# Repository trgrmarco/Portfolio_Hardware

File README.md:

# Portfolio_Hardware
Hi, this is my portfolio with some of the designs i have done

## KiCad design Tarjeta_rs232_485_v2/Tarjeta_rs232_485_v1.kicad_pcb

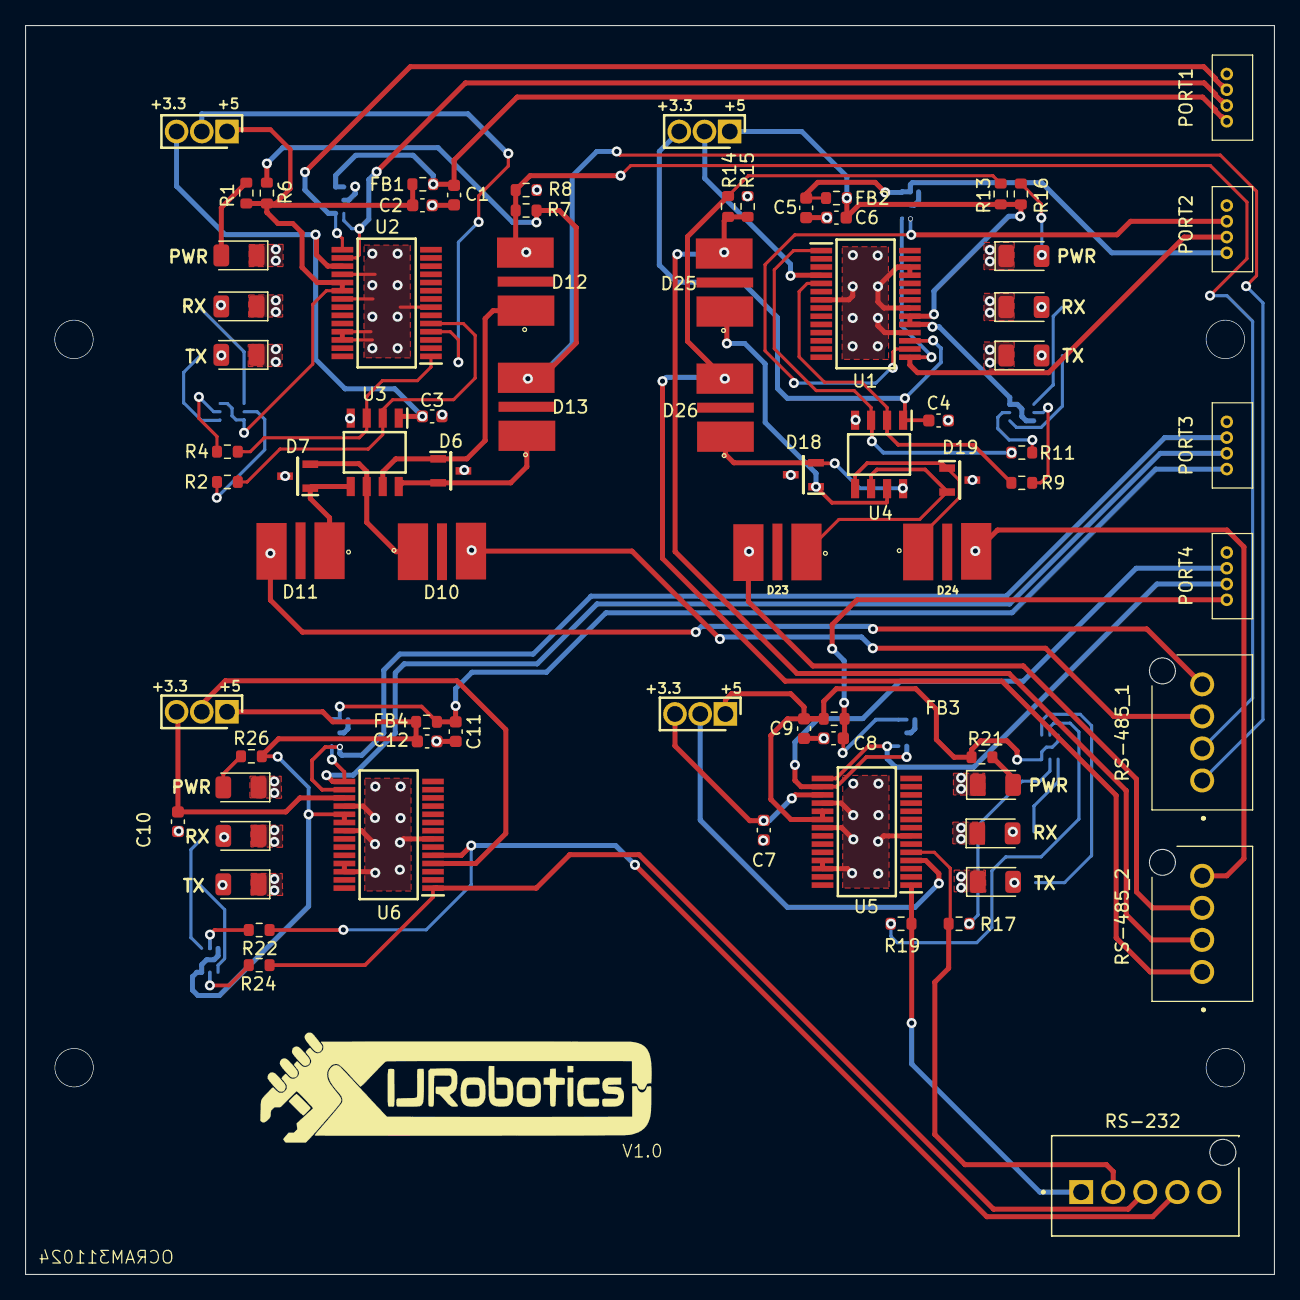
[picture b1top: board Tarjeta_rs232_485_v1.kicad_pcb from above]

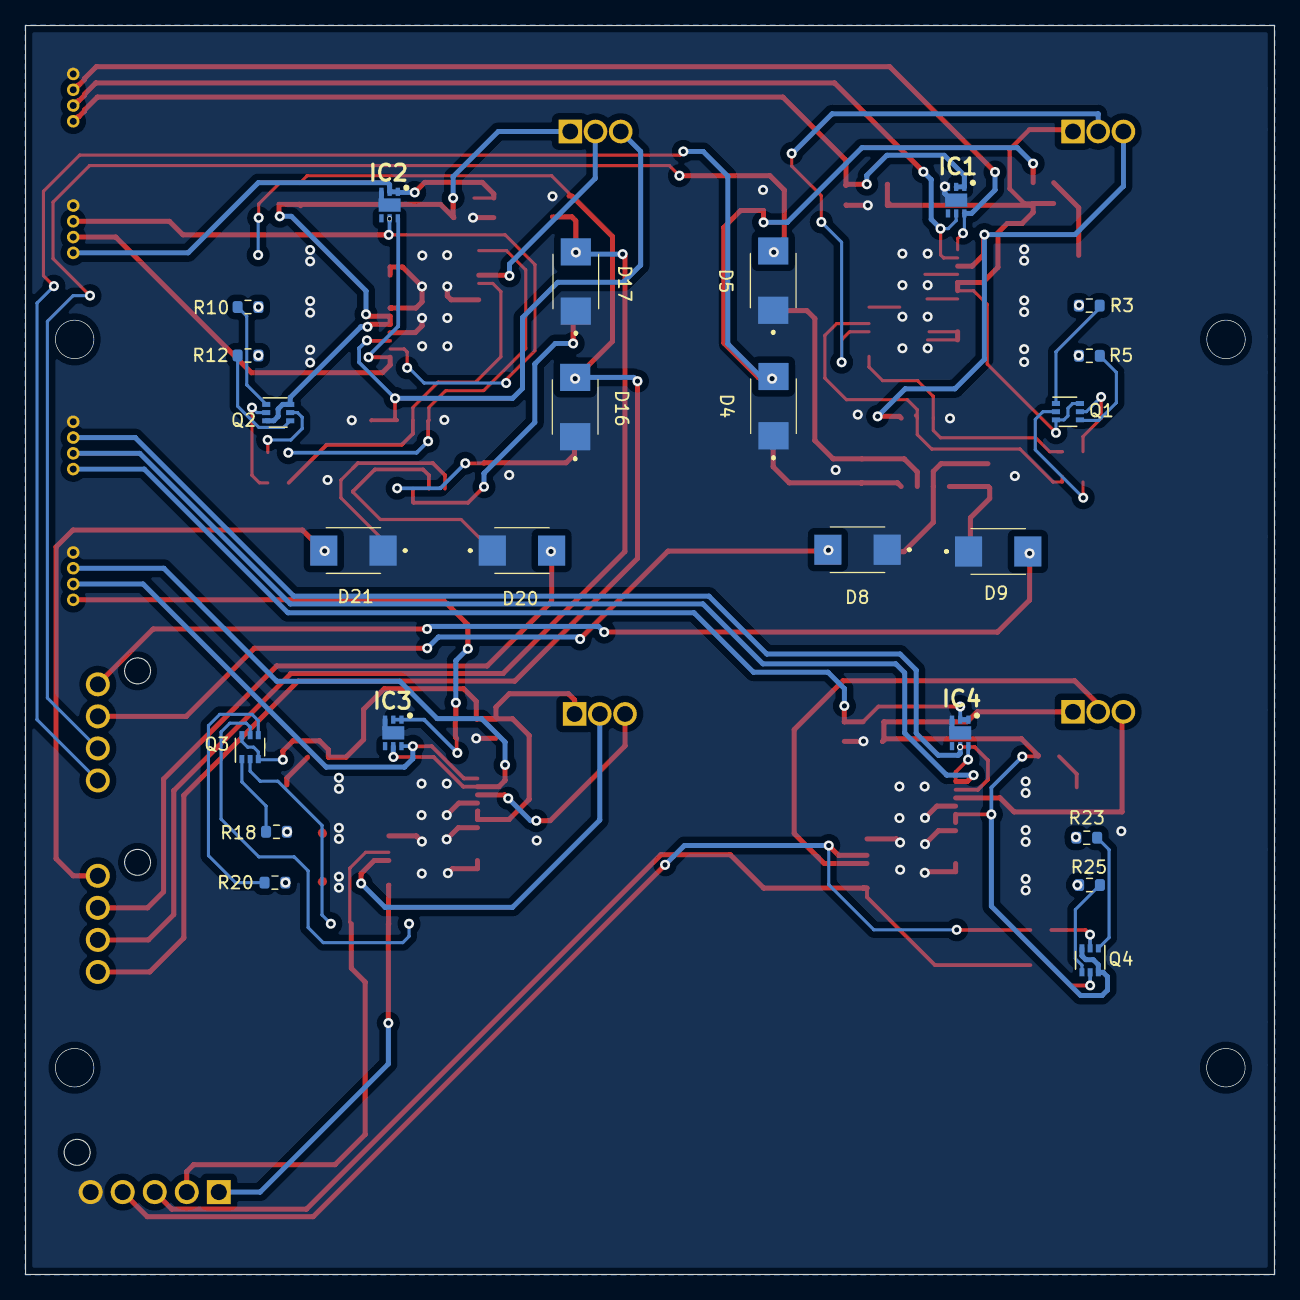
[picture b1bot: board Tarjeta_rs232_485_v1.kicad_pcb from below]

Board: 2 copper layers, 99.0 x 99.0 mm, 99 parts (24 on the bottom side), 77 nets.

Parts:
+3.3     +5, +3.3    +5, +3.3    +5#2, +3.3    +5#3: Conn_01x03; JUMPER 3POS
C1, C5, C8, C11: 10nF; C_0603_1608Metric
C2, C6, C9, C12: 4.7uF; C_0603_1608Metric
C3, C4, C7, C10: 0.1uF; C_0603_1608Metric
D4, D5, D8, D9, D16, D17, D20, D21: TISP4240M3BJR-S; TISP4240M3BJRS
D6, D7, D18, D19: CDSOT23-SM712
D10, D11, D12, D13, D23, D24, D25, D26: TBU-CA065-200-WH-; TBU-CA065-200-WH
FB1, FB2, FB3, FB4: 60 ohms; R_0603_1608Metric
IC1, IC2, IC3, IC4: D5V0F3B6LP20-7
PORT1, PORT2, PORT3, PORT4: Conn_01x04; 530470410
PWR: LED; LED_1206_3216Metric
PWR#2, PWR#3, PWR#4: LED; LED_1206_3216Metric
Q1, Q2, Q3, Q4: MBT3906DW1; SOT-363_SC-70-6
R1, R3, R5, R10, R12, R16, R18, R20, R21, R23, R25, R26: 330; R_0603_1608Metric
R2, R4, R9, R11, R17, R19, R22, R24: 10K; R_0603_1608Metric
R6, R8, R13, R15: 560; R_0603_1608Metric
R7, R14: 120; R_0603_1608Metric
RS-232: Conn_01x05; 2-644486-5
RS-485_1, RS-485_2: Conn_01x04; 26444864
RX: LED; LED_1206_3216Metric
RX#2, RX#3, RX#4: LED; LED_1206_3216Metric
TX: LED; LED_1206_3216Metric
TX#2, TX#3, TX#4: LED; LED_1206_3216Metric
U1, U2, U5, U6: FT232RNL-TUBE
U3, U4: ADM3490ExR; ADM3490

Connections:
+3.3V_1: +3.3 +5#3.3, C3.1, U2.17, U3.1
+3.3V_2: +3.3 +5#2.3, C4.1, U1.17, U4.1
+3.3V_3: +3.3 +5.3, C7.1, U5.17
+3.3V_4: +3.3 +5.3, C10.1, U6.17
+5V_1: +3.3 +5#3.1, C2.1, FB1.1, Q1.3, Q1.6, R1.2, R6.2, U2.19, U2.20
+5V_2: +3.3 +5#2.1, C6.1, FB2.1, Q2.3, Q2.6, R13.2, R16.2, U1.19, U1.20
+5V_3: +3.3 +5.1, C9.1, FB3.1, Q3.3, Q3.6, R21.2, U5.19, U5.20
+5V_4: +3.3 +5.1, C12.1, FB4.1, Q4.3, Q4.6, R26.2, U6.19, U6.20
+5V_USB_1: C1.1, FB1.2, IC1.1, IC1.2, PORT1.1
+5V_USB_2: C5.1, FB2.2, IC2.1, IC2.2, PORT2.1
+5V_USB_3: C8.1, FB3.2, IC3.1, IC3.2, PORT4.1
+5V_USB_4: C11.1, FB4.2, IC4.1, IC4.2, PORT3.1
AP_1: D6.2, D13.1, U3.8
AP_2: D18.2, D26.1, U4.8
A_1: D4.2, D13.3, R6.1, R7.2, RS-485_1.1
A_2: D16.2, D26.3, R13.1, R14.2, RS-485_2.1
BP_1: D6.1, D12.1, U3.7
BP_2: D18.1, D25.1, U4.7
B_1: D5.2, D12.3, R7.1, R8.2, RS-485_1.2
B_2: D17.2, D25.3, R14.1, R15.2, RS-485_2.2
D+_1: IC1.6, PORT1.3, U2.15
D+_2: IC2.6, PORT2.2, U1.15
D+_3: IC3.6, PORT4.2, U5.15
D+_4: IC4.6, PORT3.2, U6.15
D-_1: IC1.5, PORT1.2, U2.16
D-_2: IC2.5, PORT2.3, U1.16
D-_3: IC3.5, PORT4.3, U5.16
D-_4: IC4.5, PORT3.3, U6.16
GND: C1.2, C2.2, C3.2, C4.2, C5.2, C6.2, C7.2, C8.2, C9.2, C10.2, C11.2, C12.2, D4.1, D5.1, D6.3, D7.3, D8.1, D9.1, D16.1, D17.1, D18.3, D19.3, D20.1, D21.1, IC1.3, IC1.7, IC2.3, IC2.7, IC3.3, IC3.7, IC4.3, IC4.7, PORT1.4, PORT2.4, PORT3.4, PORT4.4, PWR.1, PWR#2.1, PWR#3.1, PWR#4.1, R8.1, R15.1, RS-232.5, RX.1, RX#2.1, RX#3.1, RX#4.1, TX.1, TX#2.1, TX#3.1, TX#4.1, U1.7, U1.18, U1.21, U1.25, U1.26, U2.7, U2.18, U2.21, U2.25, U2.26, U3.4, U4.4, U5.7, U5.18, U5.21, U5.25, U5.26, U6.7, U6.18, U6.21, U6.25, U6.26
unnamed: PWR#4.2, R1.1
unnamed: R3.2, RX#4.2
unnamed: R5.2, TX#4.2
unnamed: R10.2, RX#3.2
unnamed: R12.2, TX#3.2
unnamed: PWR#3.2, R16.1
unnamed: R18.2, RX#2.2
unnamed: R20.2, TX#2.2
unnamed: PWR#2.2, R21.1
unnamed: R23.2, RX.2
unnamed: R25.2, TX.2
unnamed: PWR.2, R26.1
unnamed: Q1.1, R3.1
unnamed: Q1.2, R2.1
unnamed: Q1.4, R5.1
unnamed: Q1.5, R4.1
unnamed: Q2.1, R10.1
unnamed: Q2.2, R9.1
unnamed: Q2.4, R12.1
unnamed: Q2.5, R11.1
unnamed: Q3.1, R18.1
unnamed: Q3.2, R17.1
unnamed: Q3.4, R20.1
unnamed: Q3.5, R19.1
unnamed: Q4.1, R23.1
unnamed: Q4.2, R22.1
unnamed: Q4.4, R25.1
unnamed: Q4.5, R24.1
RX_485_1: R2.2, U2.5, U3.2
RX_REEL: R22.2, RS-232.4, U6.5
RX_REEL_1: R17.2, RS-232.2, U5.5
RX_ROBOT: R9.2, U1.5, U4.2
TX_485_1: R4.2, U2.1, U3.3
TX_REEL: R24.2, RS-232.3, U6.1
TX_REEL_1: R19.2, RS-232.1, U5.1
TX_ROBOT: R11.2, U1.1, U4.3
VCCIO_1: +3.3 +5#3.2, U2.4
VCCIO_2: +3.3 +5#2.2, U1.4
VCCIO_3: +3.3 +5.2, U5.4
VCCIO_4: +3.3 +5.2, U6.4
YP_1: D7.1, D11.1, U3.5
YP_2: D19.1, D24.1, U4.5
Y_1: D9.2, D11.3, RS-485_1.4
Y_2: D21.2, D24.3, RS-485_2.4
ZP_1: D7.2, D10.1, U3.6
ZP_2: D19.2, D23.1, U4.6
Z_1: D8.2, D10.3, RS-485_1.3
Z_2: D20.2, D23.3, RS-485_2.3

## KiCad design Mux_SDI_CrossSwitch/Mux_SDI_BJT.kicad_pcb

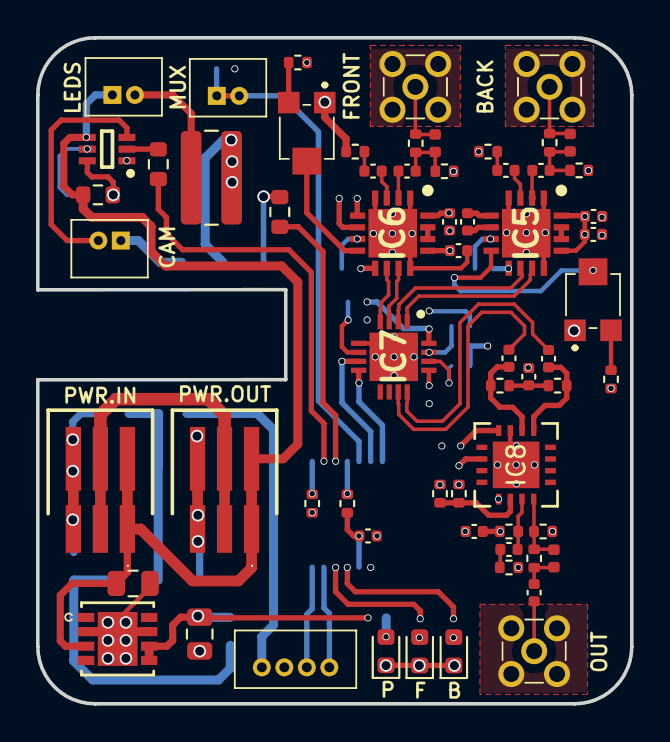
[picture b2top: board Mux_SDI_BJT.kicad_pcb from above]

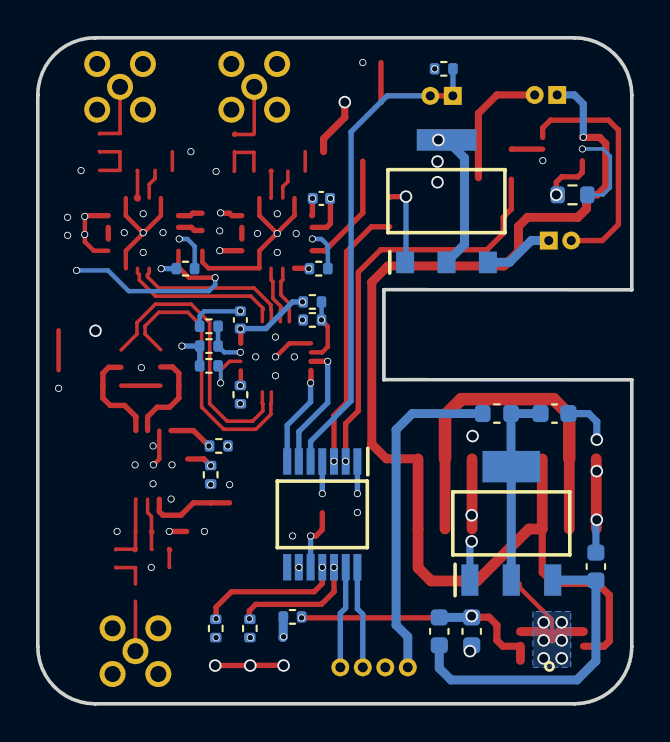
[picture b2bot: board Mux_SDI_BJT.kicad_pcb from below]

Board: 4 copper layers, 33.0 x 37.0 mm, 88 parts (25 on the bottom side), 71 nets.

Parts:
C1: 0.47uF; C_0805_2012Metric
C2: 22uF; C_0805_2012Metric
C3, C4, C5, C6, C7, C8, C9, C10, C11, C12, C13, C14, C15, C16: 1uF; C_0402_1005Metric
C17: 0.1uF; C_0402_1005Metric
C18, C19: 4.7uF; C_0402_1005Metric
C20: 1uF; C_0603_1608Metric
C21, C22: 10uF; C_0603_1608Metric
C23: 100nF; C_0402_1005Metric
D1, D2, D3: LED; LED_0603_1608Metric
F1: .8A; Fuse_0603_1608Metric
FB1: 1K; C_0603_1608Metric
IC1: FFB2227A; SOT65P210X110-6N
IC5, IC6: LMH0344SQ_NOPB
IC7: DS25CP102TSQ_NOPB; DS25CP102TSQNOPB
IC8: LMH0302SQ; LMH0302SQNOPB
IC9: STM32L011D3P6
J1: FRONT; 734151472
J2, J3, J10: 53047-0210
J4: BACK; 734151472
J5: OUT; 734151472
J6, J7: 87438-0343; 874380343
J12: Conn_01x04; 530470410
L1, L2: 5.6nH; L_0402_1005Metric
L3: 6.8nH; L_0402_1005Metric
PS1: LM2940LD-5.0_NOPB; DFN400X400X80-9N
Q1: NJT4031NT1G
R1: 1.7K; R_0603_1608Metric
R2, R3, R4: 1K; R_0603_1608Metric
R5: 33, 1W; R_1020_2550Metric
R6: 560; R_0402_1005Metric
R7, R8, R11, R18, R19, R23: 10K; R_0402_1005Metric
R9, R10: 330; R_0402_1005Metric
R12, R13, R14, R15, R36, R37, R38, R39: 75; R_0402_1005Metric
R16, R17: 37.4; R_0402_1005Metric
R20, R21: 5.6K; R_0402_1005Metric
R22: 750; R_0402_1005Metric
R24, R25, R26, R27, R28, R29, R31, R32: 0; R_0402_1005Metric
R34, R35: 50; R_0402_1005Metric
RV1, RV2: 10K; 35WR100KLFTR
U1: AMS1117-3.3; REG1117-3.3

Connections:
+3.3V: C8.1, C10.1, C11.2, C12.2, C13.2, C14.1, C23.2, F1.2, IC5.13, IC5.16, IC6.13, IC6.16, IC7.16, IC8.9, IC9.10, J12.4, R7.1, R20.1, R21.1, R22.2, R23.2, R24.1, R26.1, R28.1, R32.1, R36.2, R38.1
+5V: C2.1, C20.1, FB1.1, PS1.5, PS1.6, R6.2
+12V: C1.1, IC1.4, J2.1, J6.1, J6.4, J7.1, J7.4, PS1.3, R4.2
+24V: J6.2, J6.5, J7.2, J7.5
+CAM: IC1.3, J3.2
+VIDEO_IN0: J1.1, L2.1, R13.2
+VIDEO_IN1: J4.1, L1.1, R12.2
B_CAMON: IC9.2, R2.2
EN0: IC7.14, R32.2
EN1: IC7.13, R31.2
EQ: IC7.6, R26.2, R27.2
GND: C1.2, C2.2, C8.2, C10.2, C11.1, C12.1, C13.1, C14.2, C17.1, C20.2, C21.2, C22.2, C23.1, D1.1, D2.1, D3.1, IC1.1, IC5.1, IC5.4, IC5.9, IC5.12, IC5.17, IC6.1, IC6.4, IC6.9, IC6.12, IC6.17, IC7.5, IC7.17, IC8.3, IC8.17, IC9.9, J1.2, J1.3, J1.4, J1.5, J3.1, J4.2, J4.3, J4.4, J4.5, J5.2, J5.3, J5.4, J5.5, J6.3, J6.6, J7.3, J7.6, J12.3, PS1.2, PS1.7, PS1.9, Q1.3, R8.2, R11.1, R14.1, R15.1, R16.1, R17.1, R18.2, R19.2, R25.1, R27.1, R29.1, R31.1, R37.1, RV1.1, RV2.1, U1.1
IN_MUX: IC9.5, J10.1, J10.2, R11.2
LED: J2.2, R5.1
LEDS_HIGH: IC9.3, R1.2
LED_BACK: IC9.12, R10.1
LED_FRONT: IC9.11, R9.2
NRST: IC9.4, R7.2
unnamed: C3.1, IC5.2
unnamed: C3.2, L1.2, R12.1, R14.2
unnamed: C4.1, IC6.2
unnamed: C4.2, L2.2, R13.1, R15.2
unnamed: C5.1, IC5.3
unnamed: C5.2, R16.2
unnamed: C6.1, IC6.3
unnamed: C6.2, R17.2
unnamed: C7.1, IC5.6
unnamed: C7.2, IC5.5
unnamed: C9.1, IC6.6
unnamed: C9.2, IC6.5
unnamed: C17.2, R34.1, R35.2
unnamed: C18.1, R37.2
unnamed: C18.2, IC8.11, R36.1
unnamed: C19.2, L3.2, R39.2
unnamed: C21.1, FB1.2, U1.3
unnamed: C22.1, F1.1, U1.2, U1.4
unnamed: D1.2, R6.1
unnamed: D2.2, R9.1
unnamed: D3.2, R10.2
unnamed: IC1.2, R2.1
unnamed: IC1.5, R3.1
unnamed: IC1.6, R3.2, R4.1
unnamed: IC5.7, R18.1
unnamed: IC5.8, RV1.2
unnamed: IC5.14, IC5.15
unnamed: IC6.7, R19.1
unnamed: IC6.8, RV2.2
unnamed: IC6.14, IC6.15
unnamed: IC8.4, R22.1
unnamed: IC8.6, R23.1
unnamed: IC8.12, L3.1, R38.2, R39.1
unnamed: IC9.1, R8.1
unnamed: Q1.1, R1.1
unnamed: Q1.2, Q1.4, R5.2
unnamed: R20.2, RV1.3
unnamed: R21.2, RV2.3
OUT0+: C15.2, IC7.12
OUT0-: C16.2, IC7.11
OUT0_N: C16.1, IC8.2, R35.1
OUT0_P: C15.1, IC8.1, R34.2
OUTPUT+: C19.1, J5.1
PE: IC7.15, R28.2, R29.2
SDI0+: IC6.11, IC7.3
SDI0-: IC6.10, IC7.4
SDI1+: IC5.11, IC7.1
SDI1-: IC5.10, IC7.2
SD_HD: IC8.10, R24.2, R25.2
SEL0: IC7.7, IC9.6
SEL1: IC7.8, IC9.7
SWCLK: IC9.14, J12.2
SWDIO: IC9.13, J12.1

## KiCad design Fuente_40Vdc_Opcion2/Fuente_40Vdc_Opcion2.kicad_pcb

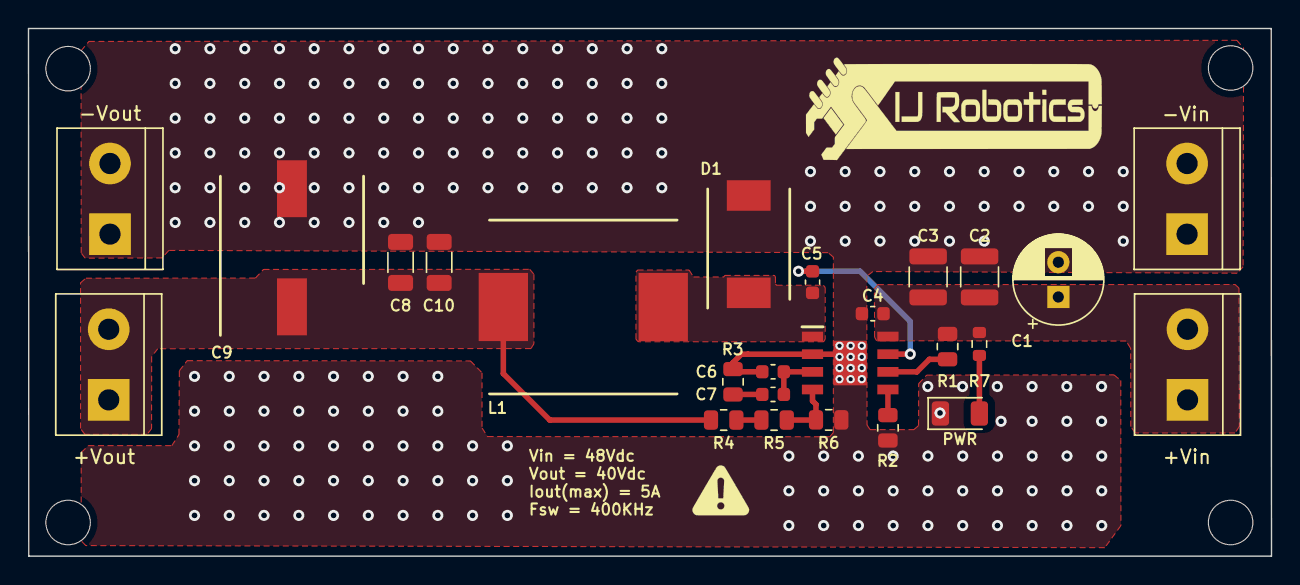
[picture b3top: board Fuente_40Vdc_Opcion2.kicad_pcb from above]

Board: 2 copper layers, 89.4 x 38.0 mm, 25 parts (0 on the bottom side), 12 nets.

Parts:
+Vin: Vin; TerminalBlock_bornier-2_P5.08mm
+Vout: Vout; TerminalBlock_bornier-2_P5.08mm
-Vin: GND; TerminalBlock_bornier-2_P5.08mm
-Vout: GND; TerminalBlock_bornier-2_P5.08mm
C1: 22uF; CP_Radial_D6.3mm_P2.50mm
C2, C3: 10uF; C_1210_3225Metric
C4, C5: 1uF; C_0603_1608Metric
C6: 0; C_0603_1608Metric
C7: 0.1nF; C_0603_1608Metric
C8, C10: 10uF; C_1206_3216Metric
C9: 120uF; A785MS127M1JLAS028
D1: 60V 6A; SK86-3G
IC1: BD9G500UEFJ-LAE2
L1: 22uH; SRP1245CC-220M
PWR: PWR; LED_1206_3216Metric
R1, R4: 0; R_0805_2012Metric
R2: 22K; R_0805_2012Metric
R3: 270K; R_0805_2012Metric
R5: 40K; R_0805_2012Metric
R6: 1K; R_0805_2012Metric
R7: 2.3K; R_0603_1608Metric

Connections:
+40V: +Vout.1, +Vout.2, C8.1, C9.1, C10.1, L1.2, R4.2
+48V: +Vin.1, +Vin.2, C1.1, C2.1, C3.1, C4.1, IC1.8, R1.1, R7.1
GND: -Vin.1, -Vin.2, -Vout.1, -Vout.2, C1.2, C2.2, C3.2, C4.2, C6.1, C8.2, C9.2, C10.2, D1.2, IC1.2, IC1.9, PWR.1, R2.1, R3.2, R6.1
unnamed: C5.1, IC1.7
unnamed: C5.2, D1.1, IC1.1, L1.1
unnamed: C6.2, C7.2, IC1.3
unnamed: C7.1, R3.1
unnamed: PWR.2, R7.2
unnamed: IC1.4, R5.1, R6.2
unnamed: IC1.5, R2.2
unnamed: IC1.6, R1.2
unnamed: R4.1, R5.2

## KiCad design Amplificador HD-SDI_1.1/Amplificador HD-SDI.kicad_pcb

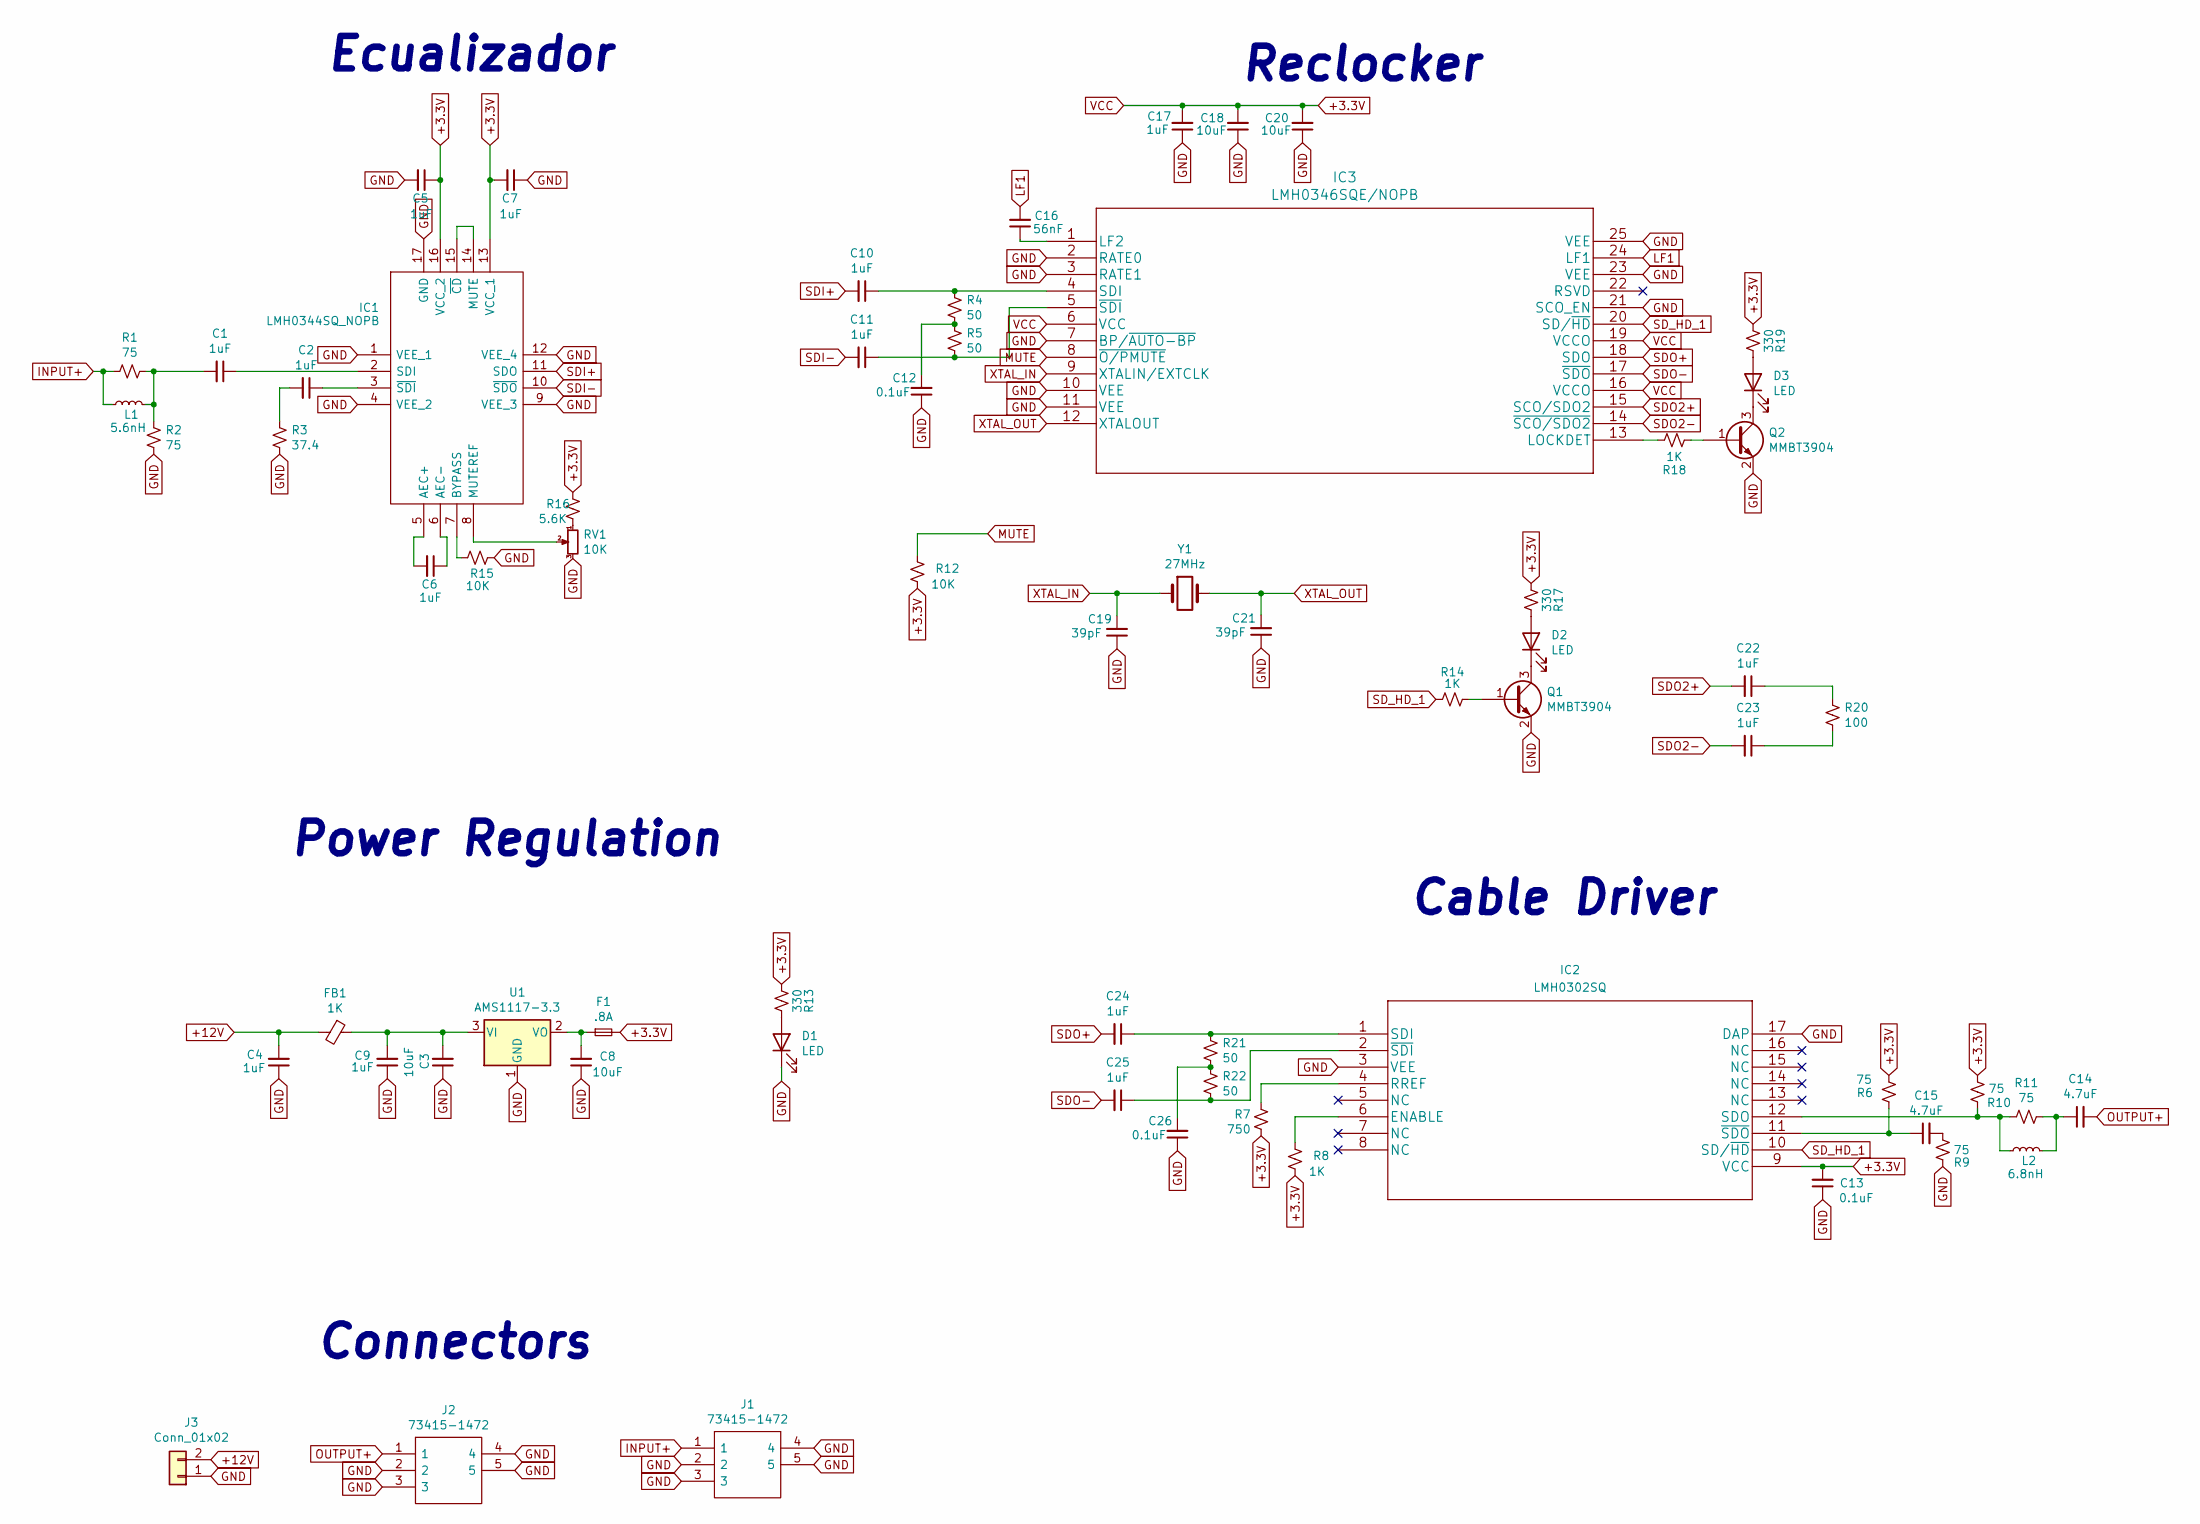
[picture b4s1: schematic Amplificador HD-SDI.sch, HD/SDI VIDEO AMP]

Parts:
C1, C2, C10, C11, C22, C23, C24, C25: 1uF; C_0402_1005Metric; Part No. KGM05AR70J105KH
C3, C8, C18, C20: 10uF; C_0603_1608Metric; Part No. GRM21BR61H106KE43K
C4, C5, C6, C7, C9, C17: 1uF; C_0603_1608Metric; Part No. CGA3E3X5R1H105K080AB
C12, C26: 0.1uF; C_0402_1005Metric; Part No. MCASU105SB5104MFNA01
C13: 0.1uF; C_0603_1608Metric; Part No. C0603C104M4RACAUTO
C14, C15: 4.7uF; C_0402_1005Metric; Part No. CM05X5R475M16AH
C16: 56nF; C_0402_1005Metric; Part No. C0402C563J4RACTU
C19, C21: 39pF; C_0603_1608Metric; Part No. C0603C390J8HACTU
D1, D2, D3: LED; LED_1206_3216Metric
F1: .8A; R_0603_1608Metric; Part No. TR-0603HV500-R
FB1: 1K; L_0603_1608Metric; Part No. FBMH1608HM102-TV
IC1: LMH0344SQ_NOPB; Part No. LMH0344SQ/NOPB
IC2: LMH0302SQ; LMH0302SQNOPB; Part No. LMH0302SQ/NOPB
IC3: LMH0346SQE/NOPB; LMH0346SQENOPB; Part No. LMH0346SQE/NOPB
J1, J2: 73415-1472; 112778; Part No. 112778
J3: Conn_01x02; 530470210; Part No. 53047-0210
L1: 5.6nH; L_0402_1005Metric; Part No. LQG15HH5N6S02D
L2: 6.8nH; L_0402_1005Metric; Part No. LQG15WZ6N8G02D
Q1, Q2: MMBT3904; SOT-23; Part No. BC847BLT1G
R1, R2, R6, R9, R10, R11: 75; R_0402_1005Metric
R3: 37.4; R_0402_1005Metric
R4, R5, R21, R22: 50; R_0402_1005Metric
R7: 750; R_0603_1608Metric
R8, R14, R18: 1K; R_0603_1608Metric
R12: 10K; R_0603_1608Metric
R13, R17, R19: 330; R_0603_1608Metric
R15: 10K; R_0402_1005Metric
R16: 5.6K; R_0603_1608Metric
R20: 100; R_0402_1005Metric
RV1: 10K; TS4YL103MR10; Part No. TS4YL103MR10
U1: AMS1117-3.3; REG1117-3.3; Part No. REG1117-3.3
Y1: 27MHz; Crystal_SMD_3225-4Pin_3.2x2.5mm; Part No. ECS-270-18-33-AEL-TR

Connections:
+3.3V: C5.1, C7.2, C13.2, C17.2, C18.2, C20.2, F1.2, IC1.13 (VCC_1), IC1.16 (VCC_2), IC2.9 (VCC), IC3.6 (VCC), IC3.16 (VCCO), IC3.19 (VCCO), R6.2, R7.1, R8.1, R10.2, R12.1, R13.1, R16.2, R17.1, R19.1
+12V: C4.2, FB1.2, J3.2
GND: C3.1, C4.1, C5.2, C7.1, C8.1, C9.1, C12.1, C13.1, C17.1, C18.1, C19.1, C20.1, C21.1, C26.1, D1.1 (K), IC1.1 (VEE_1), IC1.4 (VEE_2), IC1.9 (VEE_3), IC1.12 (VEE_4), IC1.17 (GND), IC2.3 (VEE), IC2.17 (DAP), IC3.2 (RATE0), IC3.3 (RATE1), IC3.7 (BP/~AUTO-BP), IC3.10 (VEE), IC3.11 (VEE), IC3.21 (SCO_EN), IC3.23 (VEE), IC3.25 (VEE), J1.2, J1.3, J1.4, J1.5, J2.2, J2.3, J2.4, J2.5, J3.1, Q1.2 (E), Q2.2 (E), R2.1, R3.1, R9.1, R15.2, RV1.3, U1.1 (GND)
INPUT+: J1.1, L1.1, R1.2
LF1: C16.2, IC3.24 (LF1)
MUTE: IC3.8 (~O/PMUTE), R12.2
unnamed: C1.1, IC1.2 (SDI)
unnamed: C1.2, L1.2, R1.1, R2.2
unnamed: C2.1, IC1.3 (~SDI)
unnamed: C2.2, R3.2
unnamed: C3.2, C9.2, FB1.1, U1.3 (VI)
unnamed: C6.1, IC1.6 (AEC-)
unnamed: C6.2, IC1.5 (AEC+)
unnamed: C8.2, F1.1, U1.2 (VO), U1.4
unnamed: C10.1, IC3.4 (SDI), R4.2
unnamed: C11.1, IC3.5 (~SDI), R5.1
unnamed: C12.2, R4.1, R5.2
unnamed: C14.1, L2.2, R11.1
unnamed: C15.1, IC2.11 (~SDO), R6.1
unnamed: C15.2, R9.2
unnamed: C16.1, IC3.1 (LF2)
unnamed: C22.1, R20.2
unnamed: C23.1, R20.1
unnamed: C24.1, IC2.1 (SDI), R21.2
unnamed: C25.1, IC2.2 (~SDI), R22.1
unnamed: C26.2, R21.1, R22.2
unnamed: D1.2 (A), R13.2
unnamed: D2.1 (K), Q1.3 (C)
unnamed: D2.2 (A), R17.2
unnamed: D3.1 (K), Q2.3 (C)
unnamed: D3.2 (A), R19.2
unnamed: IC1.7 (BYPASS), R15.1
unnamed: IC1.8 (MUTEREF), RV1.2
unnamed: IC1.14 (MUTE), IC1.15 (~CD)
unnamed: IC2.4 (RREF), R7.2
unnamed: IC2.6 (ENABLE), R8.2
unnamed: IC2.12 (SDO), L2.1, R10.1, R11.2
unnamed: IC3.13 (LOCKDET), R18.1
unnamed: Q1.1 (B), R14.2
unnamed: Q2.1 (B), R18.2
unnamed: R16.1, RV1.1
OUTPUT+: C14.2, J2.1
SDI+: C10.2, IC1.11 (SDO)
SDI-: C11.2, IC1.10 (~SDO)
SDO2+: C22.2, IC3.15 (SCO/SDO2)
SDO2-: C23.2, IC3.14 (~SCO/SDO2)
SDO+: C24.2, IC3.18 (SDO)
SDO-: C25.2, IC3.17 (~SDO)
SD_HD_1: IC2.10 (SD/~HD), IC3.20 (SD/~HD), R14.1
XTAL_IN: C19.2, IC3.9 (XTALIN/EXTCLK), Y1.1
XTAL_OUT: C21.2, IC3.12 (XTALOUT), Y1.2

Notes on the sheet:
Ecualizador
Reclocker
Cable Driver
Power Regulation
Connectors

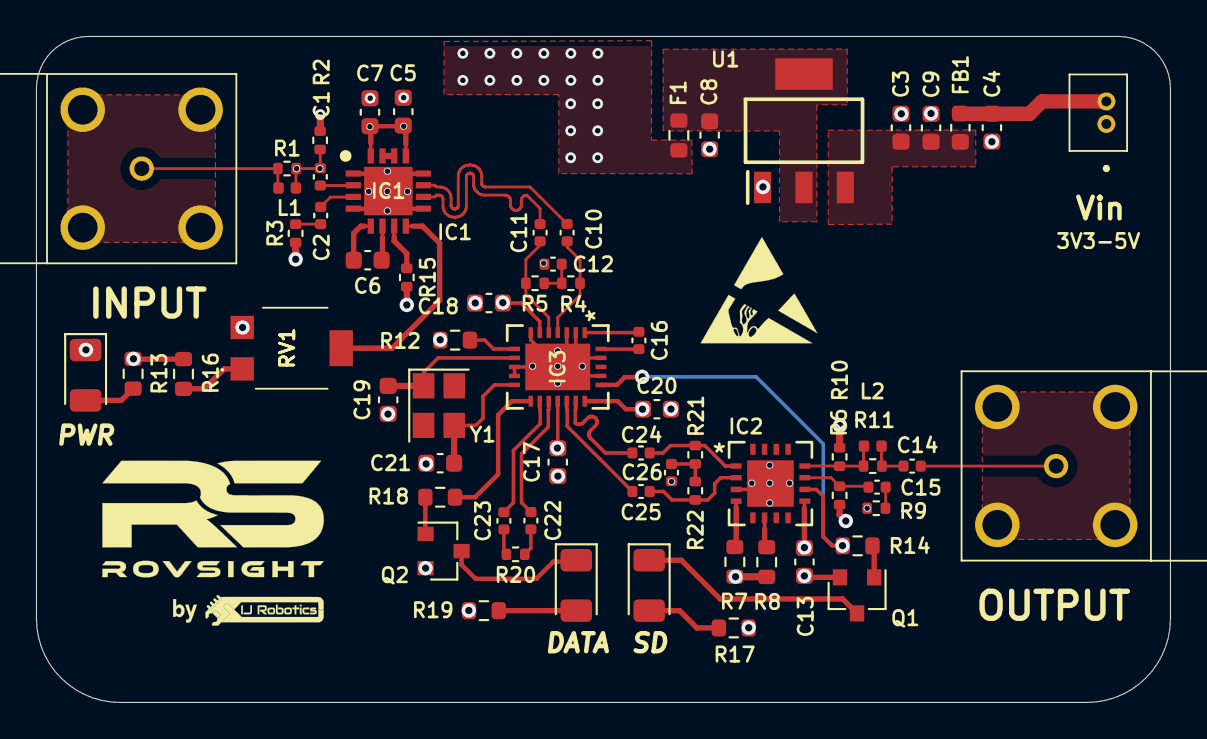
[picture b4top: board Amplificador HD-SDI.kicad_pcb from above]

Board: 4 copper layers, 63.0 x 37.0 mm, 66 parts (0 on the bottom side), 51 nets.

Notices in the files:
parts and their libraries:
Copyright 2016 Accelerated Designs. All rights reserved.
